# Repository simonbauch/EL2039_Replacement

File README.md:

# EL2039_Replacement
A replacement PCB for the commonly failing EL2039 on the AC boards of 3458As. 

This is accomplished using a THS4631DGNR from TI as the opamp in the AC amp on the A2 PCB. (like newer 3458As do) To stay in the proper operating voltage range a 3V Zener dropper is used on the -17V rail.

This replacement board passes Selftest and ACAL AC, more tests haven't been done yet. It fits mechananically below the shield.

Here in action:

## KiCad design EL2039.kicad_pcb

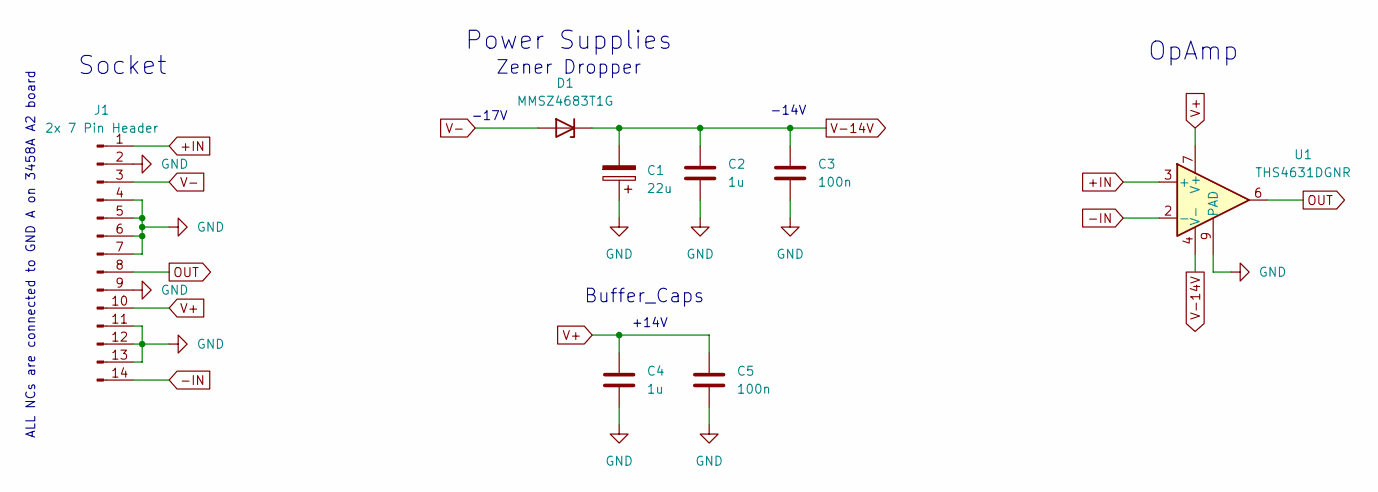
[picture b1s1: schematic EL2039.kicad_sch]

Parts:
C1: 22u; CP_EIA-6032-15_Kemet-U
C2, C4: 1u; C_0805_2012Metric
C3, C5: 100n; C_0603_1608Metric
D1: MMSZ4683T1G; D_SOD-123
J1: 2x 7 Pin Header; DIP-14_W7.62mm
U1: THS4631DGNR; MSOP-8-1EP_3x3mm_P0.65mm_EP1.5x1.8mm

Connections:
+IN: J1.1, U1.3 (+)
-IN: J1.14, U1.2 (-)
GND: C1.1, C2.2, C3.2, C4.2, C5.2, J1.2, J1.4, J1.5, J1.6, J1.7, J1.9, J1.11, J1.12, J1.13, U1.1 (NC), U1.5 (NC), U1.9 (PAD)
OUT: J1.8, U1.6
V+: C4.1, C5.1, J1.10, U1.7 (V+), U1.8 (NC)
V-: D1.2 (A), J1.3
V-14V: C1.2, C2.1, C3.1, D1.1 (K), U1.4 (V-)

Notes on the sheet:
-14V
Buffer_Caps
OpAmp
+14V
-17V
Socket
Power Supplies
ALL NCs are connected to GND A on 3458A A2 board
Zener Dropper

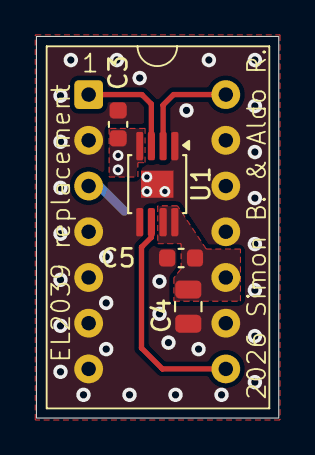
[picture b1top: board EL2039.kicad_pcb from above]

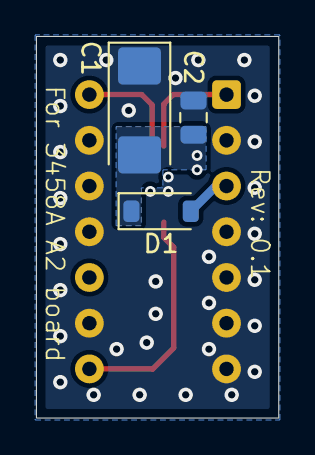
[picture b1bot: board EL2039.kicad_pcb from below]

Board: 4 copper layers, 13.5 x 21.2 mm, 8 parts (3 on the bottom side), 7 nets.

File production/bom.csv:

Designator,Footprint,Quantity,Value,LCSC Part #
C1,CP_EIA-6032-15_Kemet-U,1,22u,
"C2, C4",0805,2,1u,
"C3, C5",0603,2,100n,
D1,D_SOD-123,1,MMSZ4683T1G,
J1,DIP-14_W7.62mm,1,2x 7 Pin Header,
U1,MSOP-8-1EP_3x3mm_P0.65mm_EP1.5x1.8mm,1,THS4631DGNR,
